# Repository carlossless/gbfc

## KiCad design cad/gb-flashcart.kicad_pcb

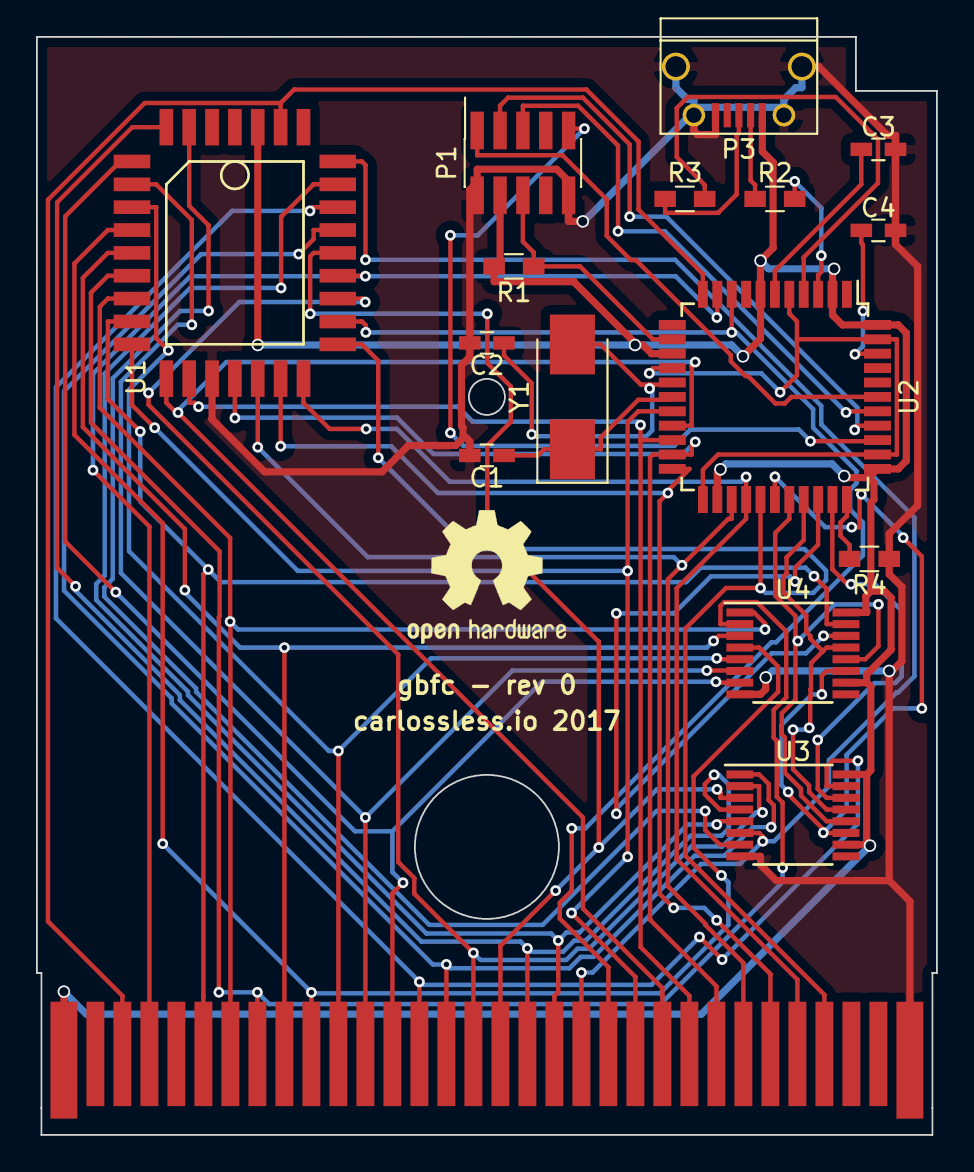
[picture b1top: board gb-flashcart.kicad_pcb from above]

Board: 2 copper layers, 50.0 x 61.0 mm, 16 parts (0 on the bottom side), 49 nets.

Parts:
C1, C2: 22pF; C_0603_HandSoldering
C3: 1uF; C_0603_HandSoldering
C4: 100nF; C_0603_HandSoldering
P1: AVR_JTAG; Socket_Strip_Straight_2x05_Pitch1.27mm_SMD
P2: GB_CART_CONNECTOR; GB_CART_FINGERS
P3: USB; USB_Micro-B
R1, R4: 10K; R_0603_HandSoldering
R2, R3: 22; R_0603_HandSoldering
U1: SST39SF010A; PLCC-32
U2: ATMEGA32U4-A; TQFP-44_10x10mm_Pitch0.8mm
U3, U4: 74HC595; TSSOP-16_4.4x5mm_Pitch0.65mm
Y1: 16Mhz; Crystal_SMD_0603-2pin_6.0x3.5mm_HandSoldering

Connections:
A0: P2.6, U1.12, U4.15
A1: P2.7, U1.11, U4.1
A2: P2.8, U1.10, U4.2
A3: P2.9, U1.9, U4.3
A4: P2.10, U1.8, U4.4
A5: P2.11, U1.7, U4.5
A6: P2.12, U1.6, U4.6
A7: P2.13, U1.5, U4.7
A8: P2.14, U1.27, U3.15
A9: P2.15, U1.26, U3.1
A10: P2.16, U1.23, U3.2
A11: P2.17, U1.25, U3.3
A12: P2.18, U1.4, U3.4
A13: P2.19, U1.28, U3.5
A14: P2.20, U1.29, U3.6
A15: U1.3, U3.7
A_OE#: U2.30, U3.13, U4.13
A_RCLK: U2.29, U3.12, U4.12
A_SER_0_7: U2.31, U4.14
A_SER_8_15: U2.32, U3.14
A_SRCLK: U2.28, U3.11, U4.11
CE#: P2.21, U1.22, U2.9
D0: P2.22, U1.13, U2.18
D1: P2.23, U1.14, U2.19
D2: P2.24, U1.15, U2.20
D3: P2.25, U1.17, U2.21
D4: P2.26, U1.18, U2.25
D5: P2.27, U1.19, U2.22
D6: P2.28, U1.20, U2.26
D7: P2.29, U1.21, U2.27
GND: C1.2, C2.2, C3.2, C4.2, P1.2, P1.10, P2.32, P3.5, P3.6, R4.1, U1.16, U3.8, U4.8
unnamed: C1.1, U2.17, Y1.1
unnamed: C2.1, U2.16, Y1.2
unnamed: C3.1, U2.6
unnamed: C4.1, U2.42
unnamed: P3.2, R2.1
unnamed: P3.3, R3.1
unnamed: R4.2, U2.33
unnamed: U2.5, U2.15, U2.23, U2.35, U2.43
OE#: P2.4, U1.24, U2.10
RST: P1.6, R1.1, U2.13
TCK: P1.1, U2.39
TDI: P1.9, U2.36
TDO: P1.3, U2.37
TMS: P1.5, U2.38
USB_D+: R3.2, U2.4
USB_D-: R2.2, U2.3
VCC: P1.4, P2.1, P3.1, R1.2, U1.32, U2.2, U2.7, U2.14, U2.24, U2.34, U2.44, U3.10, U3.16, U4.10, U4.16
WE#: P2.3, U1.31, U2.11

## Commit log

2017-03-12 Initial Commit, foundational sst39sf functions work
2017-03-13 Replaced all nop macros with appropriate delays
2017-03-21 No more shorts, way cleaner code and zear's rom
2017-03-21 Wrote & Verified
2017-03-26 Verified full write & no more shorts. (#1)
    * No more shorts, way cleaner code and zear's rom
    * Wrote & Verified
2017-03-26 Removed early test case
2017-04-28 bootloader, LUFA, firmware changes to match schematic
2017-05-02 USB mass-storage device firmware and cart pcv outline adjustments
2017-05-16 A bit of cleanup
